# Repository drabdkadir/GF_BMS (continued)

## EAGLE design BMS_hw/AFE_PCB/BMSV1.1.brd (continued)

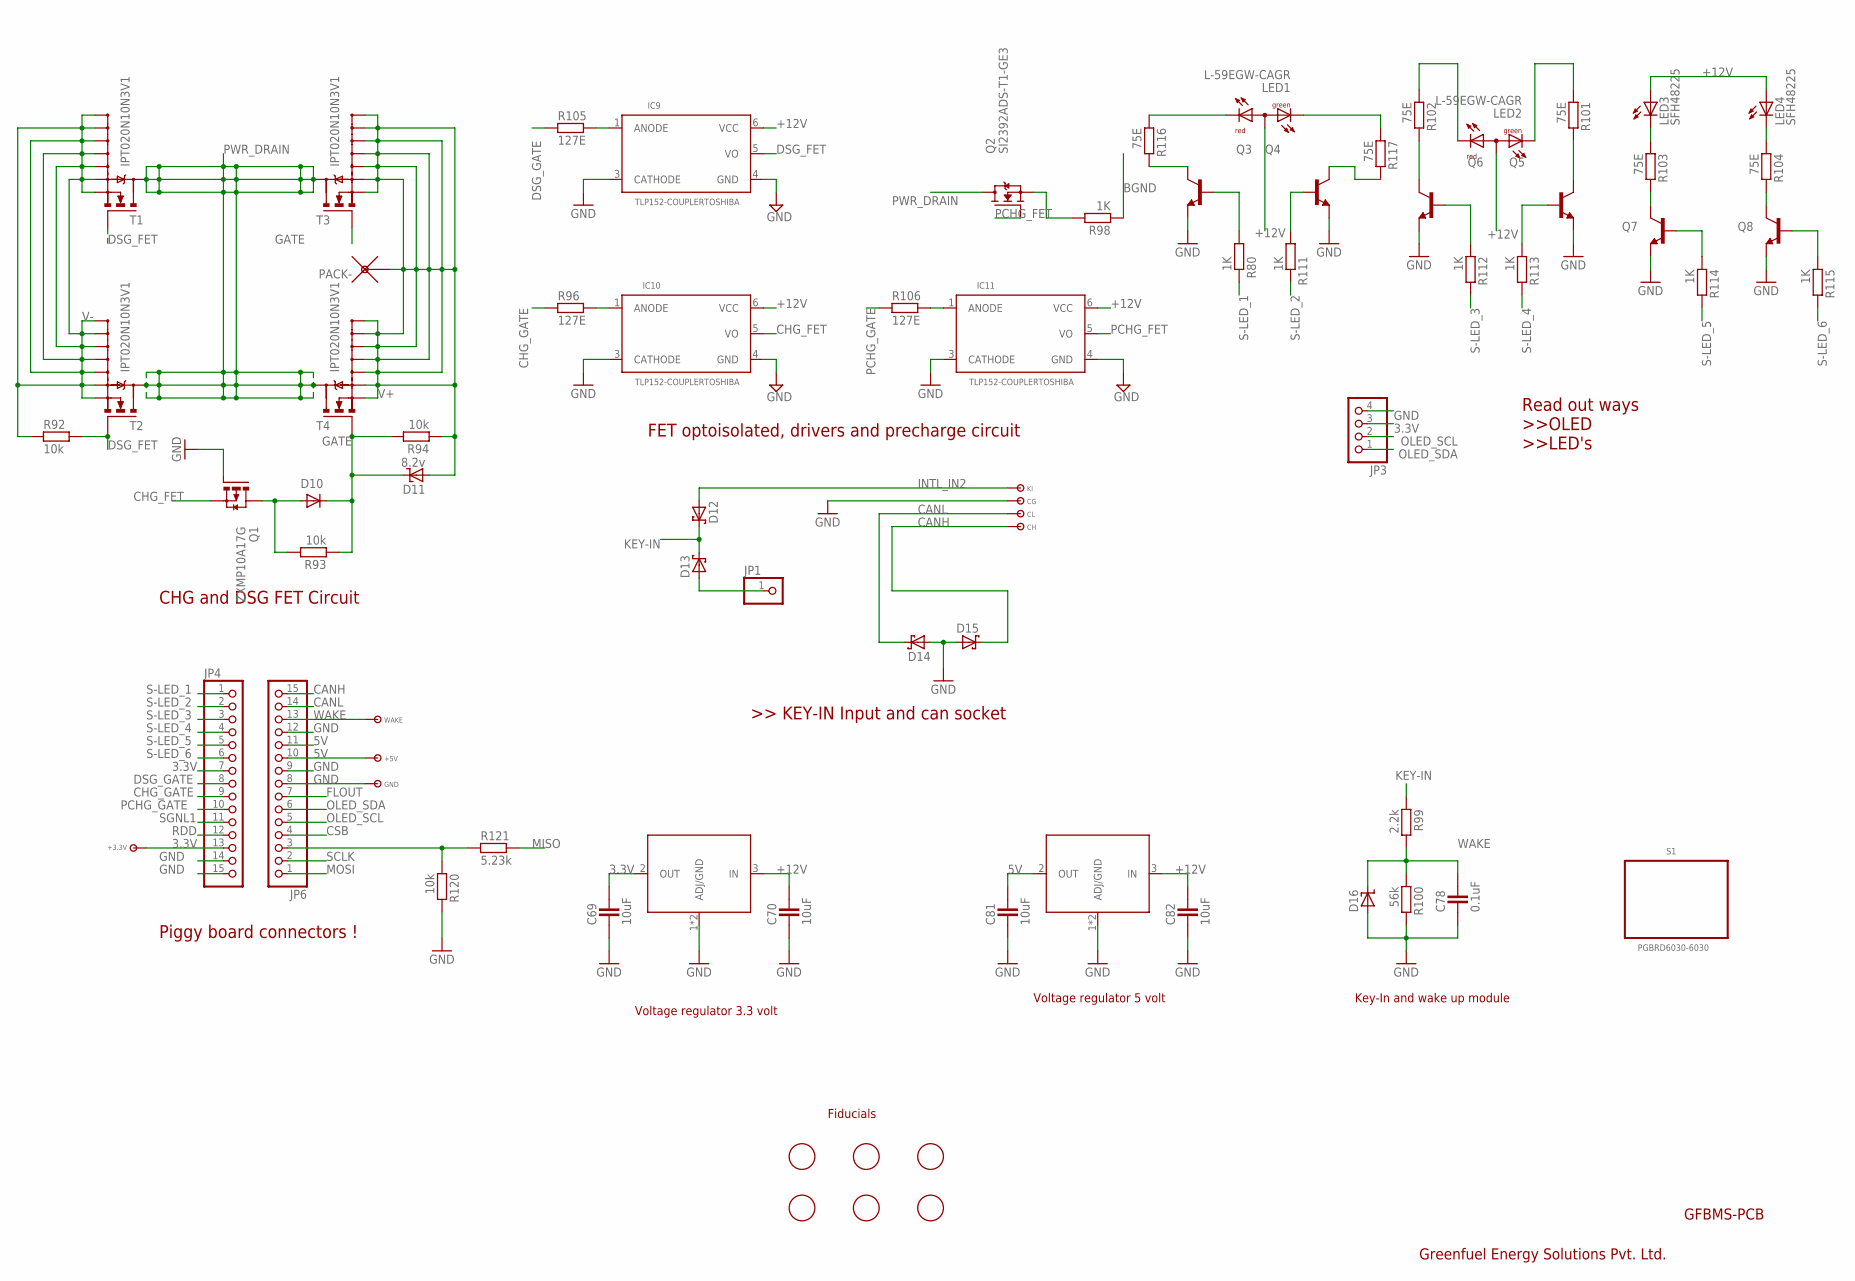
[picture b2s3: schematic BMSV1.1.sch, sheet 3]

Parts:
+3.3V, +5V: TP-SMD60
C69, C70, C81, C82: 10uF; CAPC2012X145AN
C78: 0.1uF; CAPC1608X92N
CG: TPTH7035; TP7035
CH: TPTH7035; TP7035
CL: TPTH7035; TP7035
D10: DIODE_SOD-123; SOD3718X135N
D11: 8.2v; SOD3718X135N
D12, D13, D14, D15: SCHOTTKY_SOD-123; SOD3718X135N
D16: ZENER_SOD-323; SOD2514X100N
FD1, FD2, FD3, FD4, FD5, FD6: FIDUCIAL; FIDUCIAL_1MM
GND: TP-SMD60
IC9, IC10, IC11: TLP152-COUPLERTOSHIBA; SO6-5PIN
JP1: PINHD-1X1CB; 1X01-CLEANBIG
JP3: PINOLED-4; OLED-CON
JP4, JP6: PINHD-1X15; 1X15
KI: TPTH7035; TP7035
LED1, LED2: L-59EGW-CAGR; L-59EGW-CA
LED3, LED4: SFH48225; SFH482
PACK-: WPAD
Q1: ZXMP10A17G; SOT23-3
Q2: SI2392ADS-T1-GE3; SOT23-3
Q3, Q4, Q5, Q6, Q7, Q8: NPN_SOT-23; SOT95P280X135-3N
R80, R111, R112, R113, R114, R115: 1K; RESC1005X40AN
R92, R93, R94: 10k; RESC1005X40AN
R96, R105, R106: 127E; RESC1608X55N
R98: 1K; RESC5025X70N
R99: 2.2k; RESC1608X55N
R100: 56k; RESC1608X55N
R101, R102, R103, R104, R116, R117: 75E; RESC1005X40AN
R120: 10k; RESC1608X55N
R121: 5.23k; RESC1608X55N
S1: PGBRD6030-6030; PIG6030
T1, T2, T3, T4: IPT020N10N3V1; PG-HSOF-9
U1: NCV1117ST33T3G; SOT-223
U2: NCV1117ST50T3G; SOT-223
WAKE: TP-SMD60

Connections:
3.3V: +3.3V.P$1, C69.2, JP3.3, JP4.7, JP4.13, U1.2 (OUT); also elsewhere on the board
5V: +5V.P$1, C81.2, JP6.10, JP6.11, U2.2 (OUT)
+12V: C70.2, C82.2, IC9.6 (VCC), IC10.6 (VCC), IC11.6 (VCC), LED1.2 (A), LED2.2 (A), LED3.A, LED4.A, U1.3 (IN), U2.3 (IN); also elsewhere on the board
BGND: R98.1; also elsewhere on the board
CANH: CH.P$1, D15.K, JP6.15
CANL: CL.P$1, D14.K, JP6.14
CHG_FET: IC10.5 (VO), Q1.2 (S)
CHG_GATE: JP4.9, R96.1
CSB: JP6.4; also elsewhere on the board
DSG_FET: IC9.5 (VO), R92.2, T1.1 (G), T2.1 (G)
DSG_GATE: JP4.8, R105.1
FLOUT: JP6.7; also elsewhere on the board
GATE: D10.K, D11.K, R93.1, R94.2, T3.1 (G), T4.1 (G)
GND: C69.1, C70.1, C78.1, C81.1, C82.1, CG.P$1, D14.A, D15.A, D16.A, GND.P$1, IC9.3 (CATHODE), IC9.4 (GND), IC10.3 (CATHODE), IC10.4 (GND), IC11.3 (CATHODE), IC11.4 (GND), JP3.4, JP4.14, JP4.15, JP6.8, JP6.9, JP6.12, Q1.1 (G), Q3.2 (E), Q4.2 (E), Q5.2 (E), Q6.2 (E), Q7.2 (E), Q8.2 (E), R100.2, R120.2, U1.1 (ADJ/GND), U1.4 (ADJ/GND), U2.1 (ADJ/GND), U2.4 (ADJ/GND); also elsewhere on the board
INTL_IN2: D12.A, KI.P$1
KEY-IN: D12.K, D13.K, R99.1
MISO: R121.2; also elsewhere on the board
MOSI: JP6.1; also elsewhere on the board
unnamed: D10.A, Q1.3 (D), R93.2
unnamed: IC9.1 (ANODE), R105.2
unnamed: Q7.3 (C), R103.2
unnamed: Q2.2 (S), R98.2
unnamed: Q8.3 (C), R104.2
unnamed: Q3.1 (B), R80.1
unnamed: IC10.1 (ANODE), R96.2
unnamed: IC11.1 (ANODE), R106.2
unnamed: Q4.1 (B), R111.1
unnamed: Q6.1 (B), R112.1
unnamed: Q5.1 (B), R113.1
unnamed: Q7.1 (B), R114.1
unnamed: Q8.1 (B), R115.1
unnamed: LED1.3 (CR), R116.1
unnamed: Q3.3 (C), R116.2
unnamed: LED1.1 (CG), R117.1
unnamed: Q6.3 (C), R102.2
unnamed: Q5.3 (C), R101.2
unnamed: Q4.3 (C), R117.2
unnamed: LED2.3 (CR), R102.1
unnamed: LED2.1 (CG), R101.1
unnamed: JP6.3, R120.1, R121.1
unnamed: LED4.K (C), R104.1
unnamed: LED3.K (C), R103.1
unnamed: D13.A, JP1.1
OLED_SCL: JP3.2, JP6.5
OLED_SDA: JP3.1, JP6.6
PCHG_FET: IC11.5 (VO), Q2.1 (G)
PCHG_GATE: JP4.10, R106.1
PWR_DRAIN: Q2.3 (D), T1.9 (D), T2.9 (D), T3.9 (D), T4.9 (D)
RDD: JP4.12; also elsewhere on the board
S-LED_1: JP4.1, R80.2
S-LED_2: JP4.2, R111.2
S-LED_3: JP4.3, R112.2
S-LED_4: JP4.4, R113.2
S-LED_5: JP4.5, R114.2
S-LED_6: JP4.6, R115.2
SCLK: JP6.2; also elsewhere on the board
SGNL1: JP4.11; also elsewhere on the board
V+: D11.A, PACK-.1, R94.1, T3.2 (S), T3.3 (S1), T3.4 (S2), T3.5 (S3), T3.6 (S4), T3.7 (S5), T3.8 (S6), T4.2 (S), T4.3 (S1), T4.4 (S2), T4.5 (S3), T4.6 (S4), T4.7 (S5), T4.8 (S6); also elsewhere on the board
V-: R92.1, T1.2 (S), T1.3 (S1), T1.4 (S2), T1.5 (S3), T1.6 (S4), T1.7 (S5), T1.8 (S6), T2.2 (S), T2.3 (S1), T2.4 (S2), T2.5 (S3), T2.6 (S4), T2.7 (S5), T2.8 (S6); also elsewhere on the board
WAKE: C78.2, D16.K, JP6.13, R99.2, R100.1, WAKE.P$1

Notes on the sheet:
CHG and DSG FET Circuit
Read out ways >>OLED >>LED's
FET optoisolated, drivers and precharge circuit
Piggy board connectors !
GFBMS-PCB
Greenfuel Energy Solutions Pvt. Ltd.
Key-In and wake up module
Voltage regulator 3.3 volt
Voltage regulator 5 volt
Fiducials

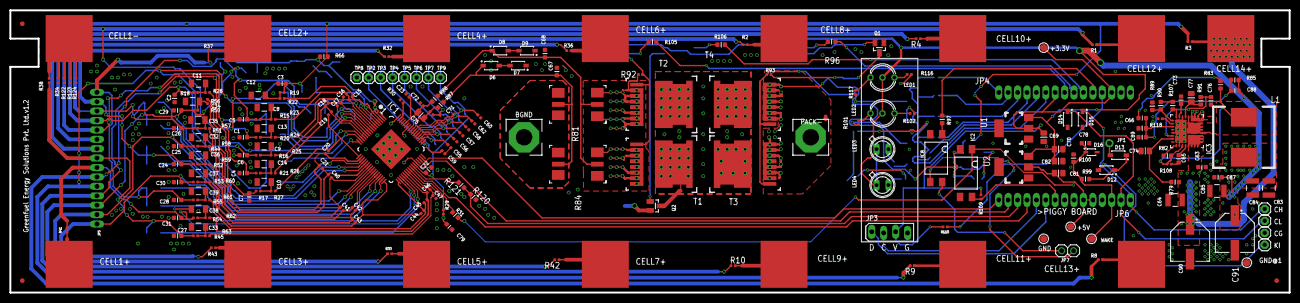
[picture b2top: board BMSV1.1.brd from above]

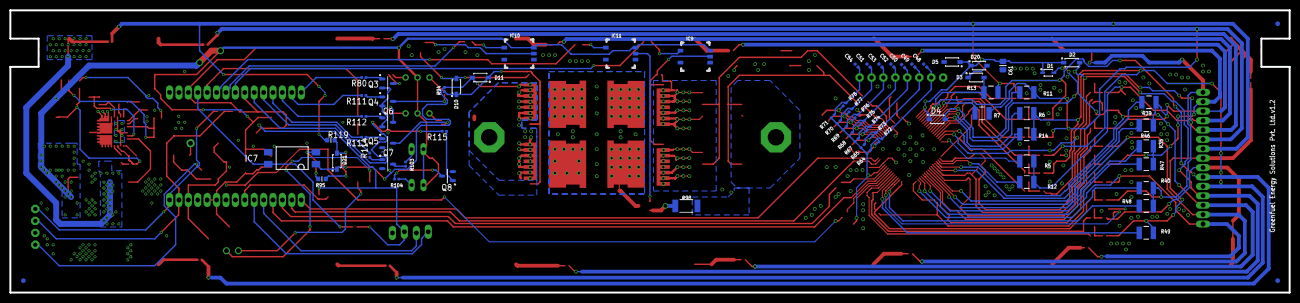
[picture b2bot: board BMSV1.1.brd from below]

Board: 2 copper layers, 272.0 x 60.0 mm, 305 parts (70 on the bottom side), 180 nets.

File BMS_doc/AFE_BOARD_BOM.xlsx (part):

GF_AFE board Revised: Sunday, OCT 14, 2018
SCH-XXXXX PDF: SPF-XXXXX Revision: 01
Item | Quantity | ASSY_OPT | Reference | Value | Description | ASSY_NOTE | Mfg Name | Mfg Part Number | PCB Footprint
1 | 17 |  | C1, C2, C3, C4, C5, C6, C7, C24, C25, C26, C27, C28, C29, C30, C31,C67, C68 | 0.047uF | CAP CER 0.047uF 100V 10% X7R AEC-Q200 0603 |  | KEMET | C0603C473K1RACAUTO | CC0603_OV | 17 | 0
2 | 18 |  | C15, C16, C17, C18, C19, C20, C21,C23, C40, C41, C42, C43, C44, C45, C46, C47,C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 | 0.047uF | CAP CER 0.047uF 50V 10% X7R AEC-Q200 0402 |  | TDK | CGA2B3X7R1H473K050BB | CC0402_25 | 18 | 0
3 | 2 |  | C22, C76 | 2.2uF | CAP CER 2.2uF 6.3V 10% X7R AEC-Q200 0603 |  | MURATA | GCM188R70J225KE22D | CC0603_OV | 2 | 0
4 | 7 |  | C48, C49, C50, C51, C52, C53, C54 | 2200pF | CAP CER 2200pF 50V 10% X7R AEC-Q200 0402 |  | MURATA | GCM155R71H222KA37D | CC0402_25 | 7 | 0
5 | 7 |  | C55,C56,C57,C58,C59,C60,C62 | 1000pF | CAP CER 1000PF 50V 10% X7R 0402 |  | AVX | 04025C102KAT2A | CC0402_25 | 7 | 0
6 | 1 |  | C61 | 0.22uF | CAP CER 0.22UF 100V 20% X7S 0805 |  | TDK | C2012X7S2A224M/SOFT | CC0805_OV | 1 | 0
7 | 3 |  | C63,C65,C66 | 0.1uF 100V | Capacitor ceramic, 10%, X7R,SMD, 0603 |  | Murata Electronics North America, Inc. | GRM188R72A104KA35D | SMD0603 | 3 | 0
8 | 1 |  | C64 | 2.2uF 100V | Capacitor cermaic, 100V, 10%, X7R, SMD, 1210 |  | KEMET | C1210C225K1RACTU | SMD1210 | 1 | 0
9 | 2 |  | C69,C81 | 10uF 25V | 10µF ±10% 25V Ceramic Capacitor X5R 0805 (2012 Metric) |  | Yageo | CC0805KKX5R8BB106 | SMD0805 | 2 | 0
10 | 2 |  | C70,C82 | 10uF 16V | 10µF ±10% 16V Ceramic Capacitor X5R 0805 (2012 Metric) |  | Yageo | CC0805KRX5R7BB106 | SMD0805 | 2 | 0
11 | 1 |  | C73 | 2.2uF 16V | Capacitor ceramic, 16V, 10%, X5R, SMD, 0603 |  | TDK Corporation | C1608X5R1C225K | SMD0603 | 1 | 0
12 | 1 |  | C74 | 1uF 100V | Capacitor ceramic, 1 µF, 100V, 10%, X7S,SMD, 0805 |  | TDK Corporation | C2012X7S2A105K125AB |  | 1 | 0
13 | 1 |  | C75 | 6.8uF | CAP CER 6.8uF 16V 10% X7S AEC-Q200 0805 |  |  | CGA4J1X7S1C685K125AC | change package to 0805 | 1 | 0
14 | 1 |  | C77 | 4.7uF 25V | Capacitor ceramic, 25V, 20%, Y5V |  | TDK Corporation | C2012Y5V1E475Z | SMD0805 | 1 | 0
15 | 2 |  | C78,C79 | 0.1uF | CAP CER 0.1UF 50V 5% X7R 0603 |  | AVX | 06035C104JAT2A | CC0603_OV | 2 | 0
16 | 15 |  | C8, C9, C10, C11, C12, C13, C14, C32, C33, C34, C35, C36, C37, C38, C39 | 0.47uF | CAP CER 0.47uF 100V 5% X7R 1206 |  | KEMET | C1206C474J1RACTU | CC1206_OV | 15 | 0
17 | 3 |  | C83, C84, C85 | 47uF 16V | Capacitor ceramic, 47 µF, 16V, 20%, X5R, SMD, 1210 |  |  | CC1210MKX5R7BB476 | SMD1210 | 3 | 0
18 | 1 |  | C87 | 0.1uF 16V | Capacitor ceramic, 10%, X7R,SMD, 0603 |  | AVX Corporation | 0603YC104KAT2A | SMD0603 | 1 | 0
19 | 1 |  | C88 | 4700pF 50V | Capacitor ceramic, 50V, 10%, X7R, SMD , 0603 |  | KEMET | C0603C472K5RACTU | SMD0603 | 1 | 0
20 | 1 | DNP | C89 | 10pF 50V | Capacitor ceramic, 50V, SMD , 0603 |  | TDK Corporation | C1608C0G1H100D | SMD0603 | 1 | 0
21 | 1 |  | C90 | 39uF 100V | Capacitor aluminum, 39 µF, 100V, 20%, RAD |  |  |  | POLAR CAP SMD | 1 | 0
 | 1 |  | C91 | 330uF 25V |  |  |  |  |  | 1 | 0
22 | 1 |  | D1 | MM3Z47VB | DIODE ZNR -- 47V 0.2W SOD323 |  | FAIRCHILD | MM3Z47VB | sod323_1A | 1 | 0
23 | 1 |  | D10 | CGRM4007-G | DIODE RECT GEN 1A 1000V SMA |  | COMCHIP TECHNOLOGY CO., LTD | CGRM4007-G | sod123_b | 1 | 0
24 | 4 |  | D12,D13,D14,D15 | MMSZ5267BT1G | DIODE ZNR 1.7MA 0.5W 75V AEC-Q101 SOD-123 |  | ON Semiconductor | MMSZ5267BT1G | SOD-123 | 4 | 0
25 | 1 |  | D16 | PDZ4.3B | DIODE ZNR 4.3V 5MA 400MW SOD323 |  | NXP Semiconductors | PDZ4.3B,115 | sod-323-A | 1 | 0
26 | 1 |  | D2 | MMSZ5257BT1G | DIODE ZNR 500mW 33V AEC-Q101 SOD123 |  | ON Semiconductor | MMSZ5257BT1G | SOD-123 | 1 | 0
27 | 4 |  | D3, D20, D21, D11 | 8.2V | DIODE ZNR 20MA 8.2V 0.5W AEC-Q101 SOD123 |  | On semiconductor | MMSZ5237BT1G | sod123 | 4 | 0
28 | 1 |  | D4 | MMSZ5257BT1G | DIODE ZNR 500mW 33V AEC-Q101 SOD123 |  | ON Semiconductor | MMSZ5257BT1G | SOD-123 | 1 | 0
29 | 1 |  | D5 | MMSZ5267BT1G | DIODE ZNR 1.7MA 0.5W 75V AEC-Q101 SOD-123 |  | ON Semiconductor | MMSZ5267BT1G | SOD-123 | 1 | 0
30 | 4 |  | D6, D7, D8, D9 | 2V | Zener Diode 2V 500mW ±5% Surface Mount SOD-123 |  |  | MMSZ4679T1G | SOD-123 | 4 | 0
31 | 1 |  | IC1 | MC33771ATP1AE | IC AUTOMOTIVE BMSIC 9.6-61.6V LQFP64 |  | FREESCALE SEMICONDUCTOR | PC33771ATP1AE | LQFP64_EP205MIL | 1 | 0
32 | 3 |  | IC2, IC7, IC8 | OPTOCOUPLER | Optoisolator Transistor Output 5300Vrms 1 Channel 4-SMD |  |  | SFH6156-3T | 4-SMD | 3 | 0
33 | 1 |  | IC3 | MIC28515T-E | MCHP Analog Switcher Buck |  | Microchip Technology Inc. | MIC28515T-E/PHA | VQFN-32 | 1 | 0
34 | 3 |  | IC9, IC10, IC11 |  | 2.5A Gate Driver Optical Coupling 3750Vrms 1 Channel 6-SO, 5 Lead |  | TOSIBHA | TLP152(TPL,E | SO6-5PIN | 3 | 0
35 | 2 |  | JP4,JP6 |  | 15 POSITION 1 ROW 2MM PITCH STRAIGHT B2B HEADERS |  |  |  | PINHD-1X15 | 2 | 0
36 | 1 |  | JP5 |  | 15 POSITION 1 ROW 2MM PITCH RIGHT ANGLE W2B HEADERS |  |  |  | PINHD-1X15 | 1 | 0
37 | 1 |  | JP7 |  | 2 POSITION 1 ROW 2.54MM PITCH STRAIGHT W2B HEADERS |  |  |  | PINHD-1X2 | 1 | 0
38 | 1 |  | L1 | BUCK COIL | Fixed Inductors MSS1278T AEC-Q200 22 uH 20% 4A Ferrite |  |  | MSS1278T-223MLD | MSS1278-D | 1 | 0
39 | 2 |  | LED1, LED2 | LED | Common Anode GREEN,Red 5MM |  |  |  | L-59EGW-CA | 2 | 0
40 | 1 |  | LED4 |  | RED LED 3MM |  |  |  | SFH482 | 1 | 0
40 | 1 |  | LED3 |  | Green LED 3MM |  |  |  | SFH482 | 1 | 0
41 | 1 |  | Q1 | 80V 2.2A | P-Channel 80V 2.2A (Tc) 3W (Tc) Surface Mount SOT-23-3 (TO-236) |  |  | SQ2337ES-T1_GE3 | sot23-3 | 1 | 0
42 | 1 |  | Q2 | 100V 3.1A | N-Channel 100V 3.1A (Tc) 1.25W (Ta), 2.5W (Tc) Surface Mount SOT-23-3 (TO-236) |  |  | SI2392ADS-T1-GE3 | SOT23-3 | 1 | 0
43 | 6 |  | Q3, Q4, Q5, Q6, Q7, Q8 | NPN 40V .2A | Bipolar (BJT) Transistor NPN 40V 200mA 300MHz 350mW Surface Mount SOT-23-3 |  | ON Semiconductor | MMBT3904 | SOT-23 | 6 | 0
44 | 18 |  | R1,R2,R3,R4,R8,R9,R10,R32,R33,R34,R36,R37,R38,R41,R42,R43, R108,R118 | 0E | RES TF ZERO OHM 1/16W AEC-Q200 RC0402 |  | VISHAY INTERTECHNOLOGY | CRCW04020000ZS | RC0402_25 | 18 | 0
45 | 1 |  | R100 | 56K |  |  |  | CRCW060356K0JNEA | SMD0402 | 1 | 0
46 | 6 |  | R101,R102,R116,R117,R103,R104 | 75E |  |  |  | RCS040275R0FKED | SMD0402 | 6 | 0
48 | 15 |  | R15, R16, R17, R18, R19, R20, R21, R44, R45, R50, R51, R52, R53, R54, R55 | 3.0K | RES MF 3.0K 1/16W 1% 0402 |  | KOA SPEER | RK73H1ETTP3001F | RC0402_25 | 15 | 0
49 | 15 |  | R22, R23, R24, R25, R26, R27, R28, R56, R57, R58, R59, R60, R61, R62, R63 | 2.00k | RES MF 2K 1/16W 1% AEC-Q200 0402 |  | KOA SPEER | RK73H1ETTP2001F | RC0402_25 | 15 | 0
50 | 14 |  | R29, R30, R64, R65, R67, R68, R69, R70, R71, R92, R93,R94,R109,R110 | 10.0K | RES MF 10.0K 1/16W 1% AEC-Q200 0402 |  | KOA SPEER | RK73H1ETTP1002F | RC0402_25 | 14 | 0
52 | 14 |  | R5, R6,R7, R11, R12, R13, R14, R35, R39, R40, R46, R47, R48, R49 | 39E | RES MF 39 OHM 0.75W 1% AEC-Q200 1210 |  | VISHAY INTERTECHNOLOGY | CRCW121039R0FKEAHP | RC1210 | 14 | 0
53 | 1 |  | R66 | 10E | RES MF 10.0 OHM 1/10W 1% 0603 |  | KOA SPEER | RK73H1JTTD10R0F | RC0603_OV | 1 | 0
54 | 7 |  | R72, R73, R74, R75, R76, R77, R78 | 1.0K | RES MF 1.0K 1/16W 1% 0402 |  | YAGEO AMERICA | RC0402FR-071KL | RC0402_25 | 7 | 0
55 | 1 |  | R79 | 2E | Resistor, TKF, 1%, 1/4W, SMD, 0603 |  | Vishay/Dale | CRCW06032R00FKEAHP | SMD0603 | 1 | 0
56 | 2 |  | R81, R84 | 200uOhm |  |  |  | LRMAP3920SUNT | LRMAP3920 | 2 | 0
57 | 1 |  | R82 | 1.6K | Resistor, 1%,1/10W, SMD, 0603 |  | Vishay/Dale | CRCW06031K60FKEA | SMD0603 | 1 | 0
58 | 1 |  | R83 | 16.2K | Resistor, TKF,1%,1/10W,SMD,0603 |  | Panasonic -ECG | ERJ-3EKF1622V | SMD0603 | 1 | 0
59 | 1 |  | R85 | 10K | Resistor, TF,1%,1/8W,SMD,0603 |  | Vishay Beyschlag | MCT06030C1002FP500 | SMD0603 | 1 | 0
60 | 1 |  | R86 | 523E |  |  |  | ERJ3EKF5230V | SMD0603 | 1 | 0
61 | 9 |  | R87, R88, R96, R105, R106,R31, R95, R97, R119 | 127E | RES MF 127 OHM 1/10W 1% 0603 |  | KOA SPEER | RK73H1JTTD1270F | RC0603_OV | 9 | 0
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
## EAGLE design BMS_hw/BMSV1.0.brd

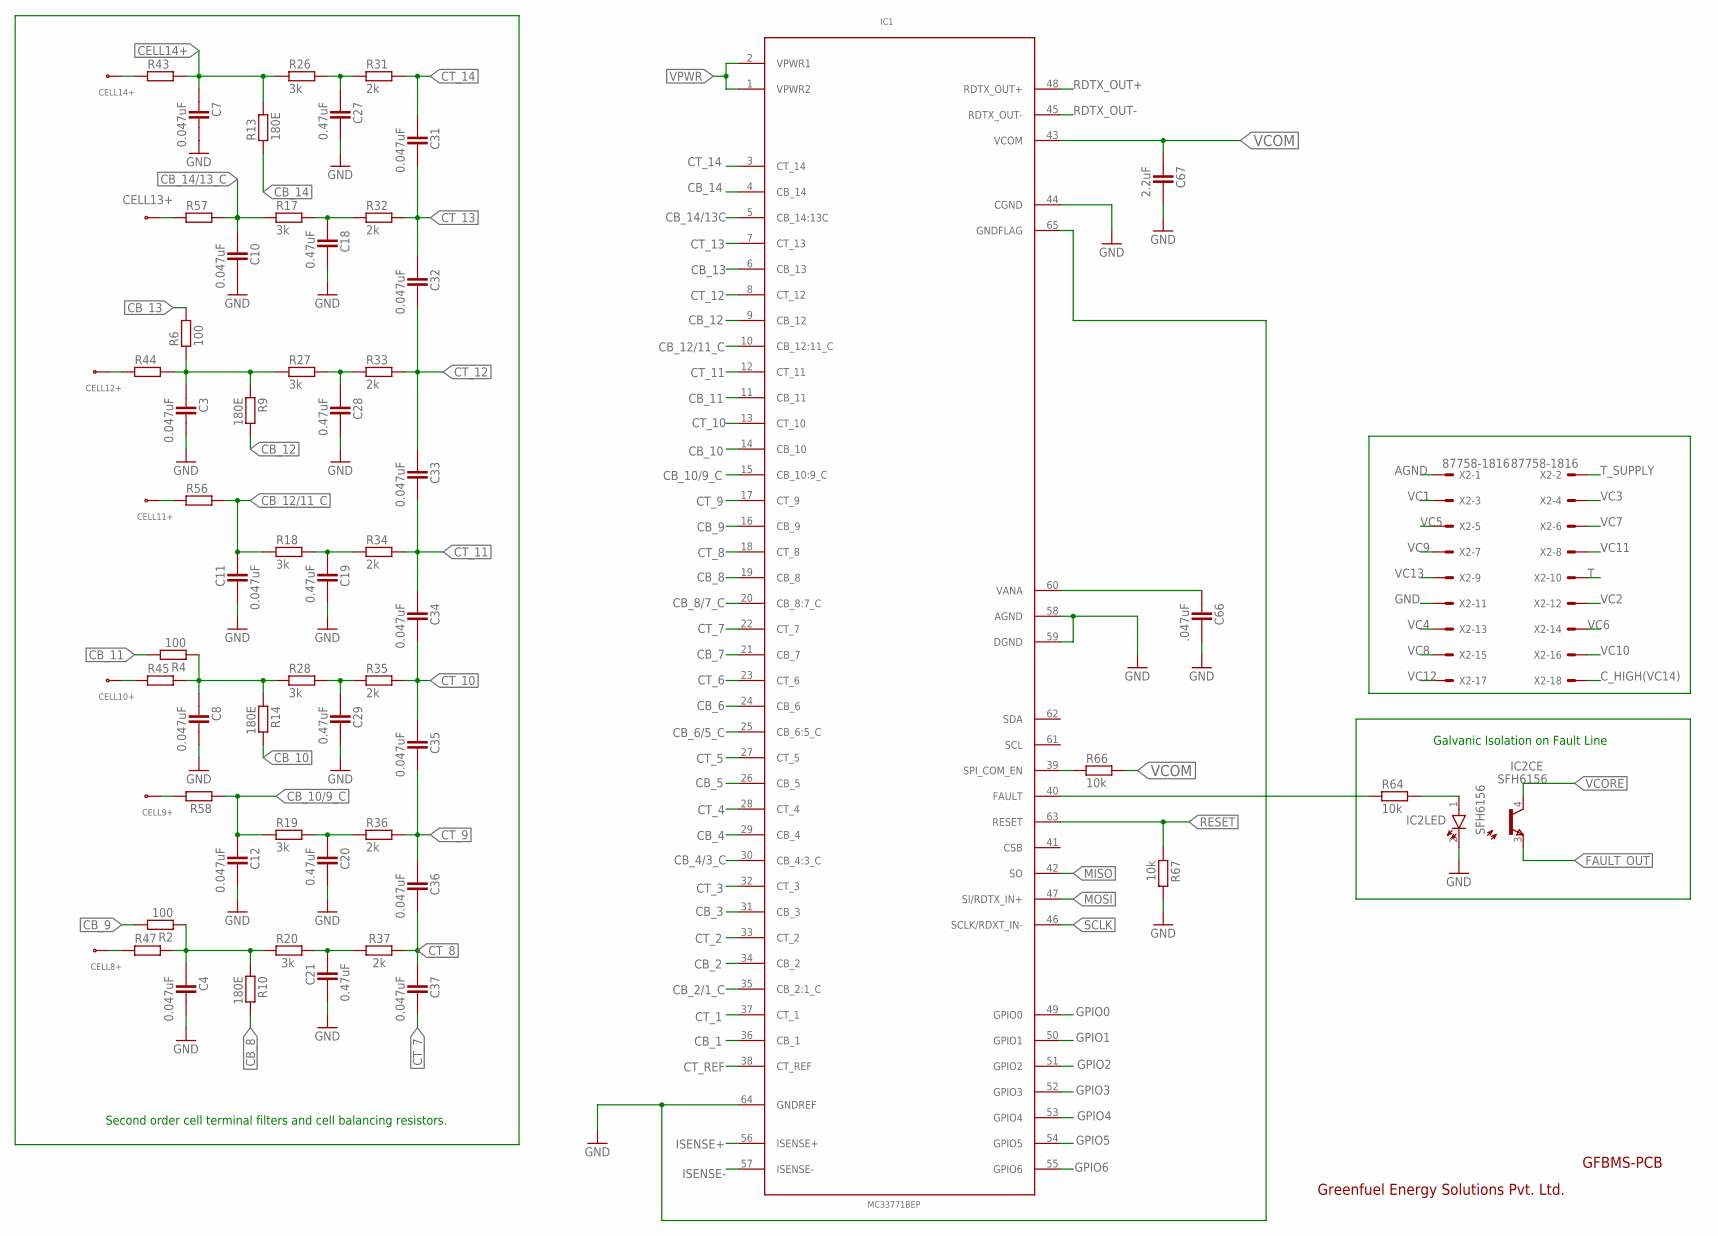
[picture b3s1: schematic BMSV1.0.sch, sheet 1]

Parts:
C3, C4, C7, C8, C10, C11, C12, C31, C32, C33, C34, C35, C36, C37: 0.047uF; CAPC1005X60N
C18, C19, C20, C21, C27, C28, C29: 0.47uF; CAPC1005X60N
C66: .047uF; CAPC1005X60N
C67: 2.2uF; CAPC1005X60N
CELL8+, CELL9+, CELL10+, CELL11+, CELL12+, CELL13+, CELL14+: GF_BMS_CELL_PADP_PAD; CELL_PAD
IC1: MC33771BEP; 64PIN-LQFP
IC2: SFH6156; SFH
R2, R4, R6: 100; RESC1005X40AN
R9, R10, R13, R14: 180E; RESC1005X40AN
R17, R18, R19, R20, R26, R27, R28: 3k; RESC1005X40AN
R31, R32, R33, R34, R35, R36, R37: 2k; RESC1005X40AN
R43, R44, R45, R47, R56, R57, R58: RESISTOR_0402; RESC1005X40AN
R64, R66, R67: 10k; RESC1005X40AN
X2: 87758-1816

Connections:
AGND: X2.1
CB_1: IC1.36 (CB_1); also elsewhere on the board
CB_2: IC1.34 (CB_2); also elsewhere on the board
CB_2/1_C: IC1.35 (CB_2:1_C); also elsewhere on the board
CB_3: IC1.31 (CB_3); also elsewhere on the board
CB_4: IC1.29 (CB_4); also elsewhere on the board
CB_4/3_C: IC1.30 (CB_4:3_C); also elsewhere on the board
CB_5: IC1.26 (CB_5); also elsewhere on the board
CB_6: IC1.24 (CB_6); also elsewhere on the board
CB_6/5_C: IC1.25 (CB_6:5_C); also elsewhere on the board
CB_7: IC1.21 (CB_7); also elsewhere on the board
CB_8: IC1.19 (CB_8), R10.2
CB_8/7_C: IC1.20 (CB_8:7_C); also elsewhere on the board
CB_9: IC1.16 (CB_9), R2.2
CB_10: IC1.14 (CB_10), R14.2
CB_10/9_C: C12.1, IC1.15 (CB_10:9_C), R19.1, R58.1; also elsewhere on the board
CB_11: IC1.11 (CB_11), R4.2
CB_12: IC1.9 (CB_12), R9.2; also elsewhere on the board
CB_12/11_C: C11.1, IC1.10 (CB_12:11_C), R18.1, R56.2
CB_13: IC1.6 (CB_13), R6.2
CB_13/12_C: C3.1, R6.1, R9.1, R27.1, R44.2
CB_13/12_C1: C8.1, R4.1, R14.1, R28.1, R45.2
CB_13/12_C2: C4.1, R2.1, R10.1, R20.1, R47.2
CB_14: IC1.4 (CB_14), R13.1; also elsewhere on the board
CB_14/13C: IC1.5 (CB_14:13C)
CB_14/13_C: C10.1, R17.1, R57.2
CELL14+: C7.1, R13.2, R26.1, R43.2; also elsewhere on the board
CT_1: IC1.37 (CT_1); also elsewhere on the board
CT_2: IC1.33 (CT_2); also elsewhere on the board
CT_3: IC1.32 (CT_3); also elsewhere on the board
CT_4: IC1.28 (CT_4); also elsewhere on the board
CT_5: IC1.27 (CT_5); also elsewhere on the board
CT_6: IC1.23 (CT_6); also elsewhere on the board
CT_7: C37.2, IC1.22 (CT_7); also elsewhere on the board
CT_8: C36.2, C37.1, IC1.18 (CT_8), R37.2
CT_9: C35.2, C36.1, IC1.17 (CT_9), R36.2
CT_10: C34.2, C35.1, IC1.13 (CT_10), R35.2
CT_11: C33.2, C34.1, IC1.12 (CT_11), R34.2
CT_12: C32.2, C33.1, IC1.8 (CT_12), R33.2
CT_13: C31.2, C32.1, IC1.7 (CT_13), R32.2
CT_14: C31.1, IC1.3 (CT_14), R31.2
CT_REF: IC1.38 (CT_REF); also elsewhere on the board
C_HIGH(VC14): X2.18
FAULT_OUT: IC2.3 (E)
GND: C3.2, C4.2, C7.2, C8.2, C10.2, C11.2, C12.2, C18.2, C19.2, C20.2, C21.2, C27.2, C28.2, C29.2, C66.2, C67.2, IC1.44 (CGND), IC1.58 (AGND), IC1.59 (DGND), IC1.64 (GNDREF), IC1.65 (GNDFLAG), IC2.2 (K), R67.2, X2.11; also elsewhere on the board
GPIO0: IC1.49 (GPIO0); also elsewhere on the board
GPIO1: IC1.50 (GPIO1); also elsewhere on the board
GPIO2: IC1.51 (GPIO2); also elsewhere on the board
GPIO3: IC1.52 (GPIO3); also elsewhere on the board
GPIO4: IC1.53 (GPIO4); also elsewhere on the board
GPIO5: IC1.54 (GPIO5); also elsewhere on the board
GPIO6: IC1.55 (GPIO6); also elsewhere on the board
ISENSE+: IC1.56 (ISENSE+); also elsewhere on the board
ISENSE-: IC1.57 (ISENSE-); also elsewhere on the board
MISO: IC1.42 (SO)
MOSI: IC1.47 (SI/RDTX_IN+)
unnamed: C27.1, R26.2, R31.1
unnamed: C21.1, R20.2, R37.1
unnamed: C29.1, R28.2, R35.1
unnamed: C28.1, R27.2, R33.1
unnamed: C18.1, R17.2, R32.1
unnamed: C20.1, R19.2, R36.1
unnamed: C19.1, R18.2, R34.1
unnamed: C66.1, IC1.60 (VANA)
unnamed 100: CELL14+.P$1, R43.1; also elsewhere on the board
unnamed: IC1.40 (FAULT), R64.1
unnamed: IC2.1 (A), R64.2
unnamed: IC1.39 (SPI_COM_EN), R66.1
unnamed: CELL12+.P$1, R44.1
unnamed: CELL10+.P$1, R45.1
unnamed: CELL8+.P$1, R47.1
unnamed: CELL11+.P$1, R56.1
unnamed: CELL13+.P$1, R57.1
unnamed: CELL9+.P$1, R58.2
RDTX_OUT+: IC1.48 (RDTX_OUT+); also elsewhere on the board
RDTX_OUT-: IC1.45 (RDTX_OUT-); also elsewhere on the board
RESET: IC1.63 (RESET), R67.1
SCLK: IC1.46 (SCLK/RDXT_IN-)
T: X2.10
T_SUPPLY: X2.2
VC1: X2.3
VC2: X2.12
VC3: X2.4
VC4: X2.13
VC5: X2.5
VC6: X2.14
VC7: X2.6
VC8: X2.15
VC9: X2.7
VC10: X2.16
VC11: X2.8
VC12: X2.17
VC13: X2.9
VCOM: C67.1, IC1.43 (VCOM), R66.2; also elsewhere on the board
VCORE: IC2.4 (C)
VPWR: IC1.1 (VPWR2), IC1.2 (VPWR1); also elsewhere on the board

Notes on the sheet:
Galvanic Isolation on Fault Line
Second order cell terminal filters and cell balancing resistors.
Greenfuel Energy Solutions Pvt. Ltd.
GFBMS-PCB

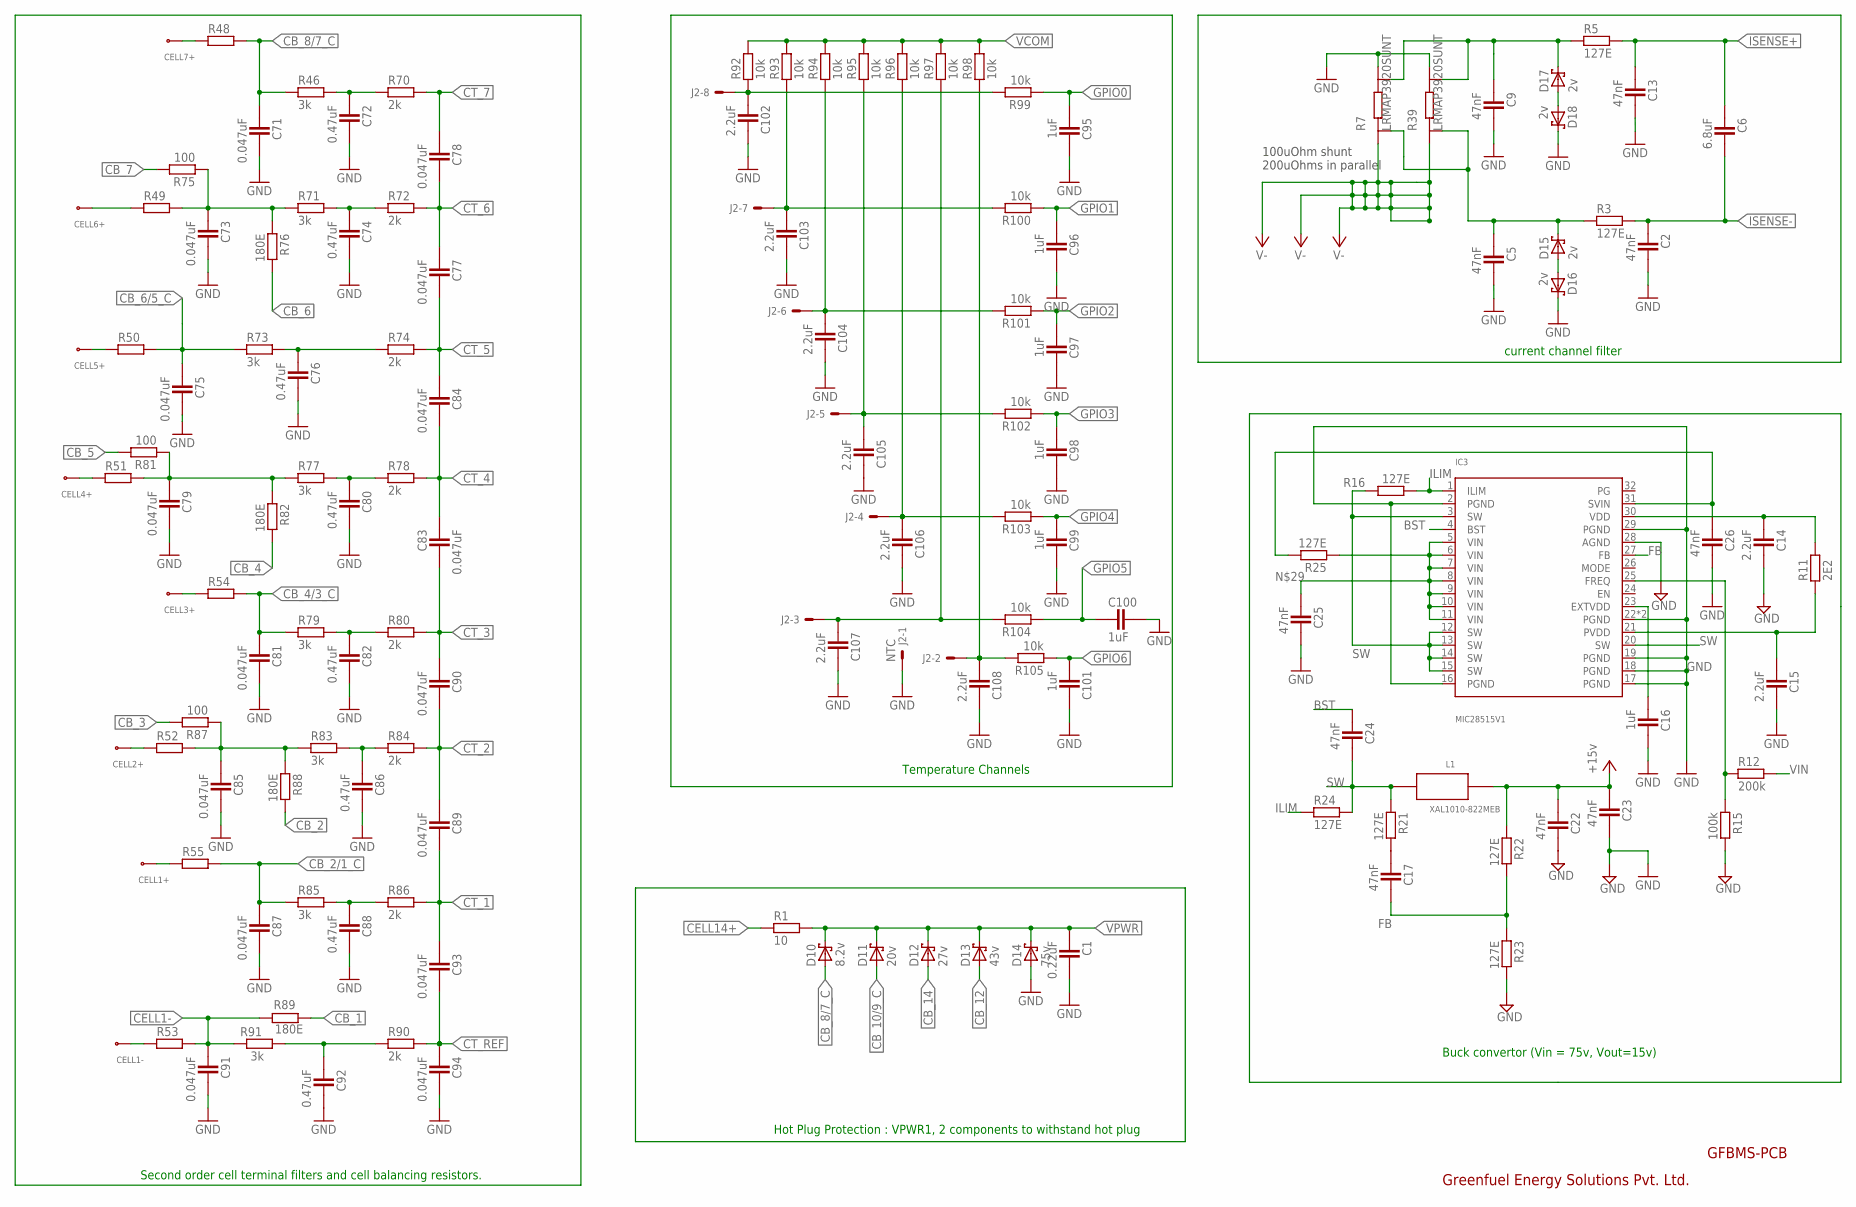
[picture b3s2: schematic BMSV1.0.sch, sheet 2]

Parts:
C1: 0.22uF; CAPC1005X60N
C2, C5, C9, C13, C17, C24, C26: 47nF; CAPC1005X60N
C6: 6.8uF; CAPC1005X60N
C14, C15, C102, C103, C104, C105, C106, C107, C108: 2.2uF; CAPC1005X60N
C16, C95, C96, C97, C98, C99, C100, C101: 1uF; CAPC1005X60N
C22: 47nF; CAPC1608X92N
C23, C25: 47nF; CAPC3225X168N
C71, C73, C75, C77, C78, C79, C81, C83, C84, C85, C87, C89, C90, C91, C93, C94: 0.047uF; CAPC1005X60N
C72, C74, C76, C80, C82, C86, C88, C92: 0.47uF; CAPC1005X60N
CELL1+, CELL1-, CELL2+, CELL3+, CELL4+, CELL5+, CELL6+, CELL7+: GF_BMS_CELL_PADP_PAD; CELL_PAD
D10: 8.2v; SOD3718X135N
D11: 20v; SOD3718X135N
D12: 27v; SOD3718X135N
D13: 43v; SOD3718X135N
D14: 75v; SOD3718X135N
D15, D16, D17, D18: 2v; SOD3718X135N
IC3: MIC28515V1; VQFN-32
J2: NTC; 6410-08
L1: XAL1010-822MEB; DUALPAD
R1: 10; RESC1005X40AN
R3, R5, R16, R21, R22, R23, R24, R25: 127E; RESC1005X40AN
R7, R39: LRMAP3920SUNT; SMD4
R11: 2E2; RESC1005X40AN
R12: 200k; RESC1005X40AN
R15: 100k; RESC1005X40AN
R46, R71, R73, R77, R79, R83, R85, R91: 3k; RESC1005X40AN
R48, R49, R50, R51, R52, R53, R54, R55: RESISTOR_0402; RESC1005X40AN
R70, R72, R74, R78, R80, R84, R86, R90: 2k; RESC1005X40AN
R75, R81, R87: 100; RESC1005X40AN
R76, R82, R88, R89: 180E; RESC1005X40AN
R92, R93, R94, R95, R96, R97, R98, R99, R100, R101, R102, R103, R104, R105: 10k; RESC1005X40AN

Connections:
BST: C24.1, IC3.4 (BST)
CB_1: R89.2; also elsewhere on the board
CB_2: R88.2; also elsewhere on the board
CB_2/1_C: C87.1, R55.2, R85.1; also elsewhere on the board
CB_3: R87.2; also elsewhere on the board
CB_4: R82.2; also elsewhere on the board
CB_4/3_C: C81.1, R54.2, R79.1; also elsewhere on the board
CB_5: R81.2; also elsewhere on the board
CB_6: R76.2; also elsewhere on the board
CB_6/5_C: C75.1, R50.2, R73.1; also elsewhere on the board
CB_7: R75.2; also elsewhere on the board
CB_8/7_C: C71.1, D10.A, R46.1, R48.2; also elsewhere on the board
CB_10/9_C: D11.A; also elsewhere on the board
CB_12: D13.A; also elsewhere on the board
CB_13/12_C6: C73.1, R49.2, R71.1, R75.1, R76.1
CB_13/12_C7: C79.1, R51.2, R77.1, R81.1, R82.1
CB_13/12_C8: C85.1, R52.2, R83.1, R87.1, R88.1
CB_14: D12.A; also elsewhere on the board
CELL1-: C91.1, R53.2, R89.1, R91.1
CELL14+: R1.1; also elsewhere on the board
CT_1: C89.2, C93.1, R86.2; also elsewhere on the board
CT_2: C89.1, C90.2, R84.2; also elsewhere on the board
CT_3: C83.2, C90.1, R80.2; also elsewhere on the board
CT_4: C83.1, C84.2, R78.2; also elsewhere on the board
CT_5: C77.2, C84.1, R74.2; also elsewhere on the board
CT_6: C77.1, C78.2, R72.2; also elsewhere on the board
CT_7: C78.1, R70.2; also elsewhere on the board
CT_REF: C93.2, C94.1, R90.2; also elsewhere on the board
FB: C17.2, IC3.27 (FB), R22.2, R23.1
GND: C1.2, C2.2, C5.2, C9.2, C13.2, C14.2, C15.2, C16.2, C22.2, C23.2, C25.2, C26.2, C71.2, C72.2, C73.2, C74.2, C75.2, C76.2, C79.2, C80.2, C81.2, C82.2, C85.2, C86.2, C87.2, C88.2, C91.2, C92.2, C94.2, C95.2, C96.2, C97.2, C98.2, C99.2, C100.2, C101.2, C102.2, C103.2, C104.2, C105.2, C106.2, C107.2, C108.2, D14.A, D16.K, D18.K, IC3.2 (PGND), IC3.16 (PGND), IC3.17 (PGND), IC3.18 (PGND), IC3.19 (PGND), IC3.22 (PGND), IC3.28 (AGND), IC3.29 (PGND), IC3.33 (PGND), J2.1, R7.4, R7.6 (4), R15.2, R23.2, R39.4, R39.6 (4); also elsewhere on the board
GPIO0: C95.1, R99.1; also elsewhere on the board
GPIO1: C96.1, R100.1; also elsewhere on the board
GPIO2: C97.1, R101.1; also elsewhere on the board
GPIO3: C98.1, R102.1; also elsewhere on the board
GPIO4: C99.1, R103.1; also elsewhere on the board
GPIO5: C100.1, R104.1; also elsewhere on the board
GPIO6: C101.1, R105.1; also elsewhere on the board
ILIM: IC3.1 (ILIM), R16.1, R24.1
ISENSE+: C6.1, C13.1, R5.2; also elsewhere on the board
ISENSE-: C2.1, C6.2, R3.2; also elsewhere on the board
unnamed: D15.A, D16.A
unnamed: C76.1, R73.2, R74.1
unnamed: D17.A, D18.A
unnamed: IC3.25 (FREQ), R12.1, R15.1
unnamed: C16.1, IC3.23 (EXTVDD)
unnamed: C26.1, IC3.31 (SVIN), R25.2
unnamed: C17.1, R21.2
unnamed 100: C25.1, IC3.5 (VIN), IC3.6 (VIN), IC3.7 (VIN), IC3.8 (VIN), IC3.9 (VIN), IC3.10 (VIN), IC3.11 (VIN), R25.1; also elsewhere on the board
unnamed: CELL6+.P$1, R49.1
unnamed: CELL5+.P$1, R50.1
unnamed: C72.1, R46.2, R70.1
unnamed: C74.1, R71.2, R72.1
unnamed: CELL7+.P$1, R48.1
unnamed: C80.1, R77.2, R78.1
unnamed: C82.1, R79.2, R80.1
unnamed: C86.1, R83.2, R84.1
unnamed: C88.1, R85.2, R86.1
unnamed: C92.1, R90.1, R91.2
unnamed: C102.1, J2.8, R92.1, R99.2
unnamed: C103.1, J2.7, R93.1, R100.2
unnamed: C104.1, J2.6, R94.1, R101.2
unnamed: C105.1, J2.5, R95.1, R102.2
unnamed: C106.1, J2.4, R96.1, R103.2
unnamed: C107.1, J2.3, R97.1, R104.2
unnamed: C108.1, J2.2, R98.1, R105.2
unnamed: CELL4+.P$1, R51.1
unnamed: CELL3+.P$1, R54.1
unnamed: CELL2+.P$1, R52.1
unnamed: CELL1+.P$1, R55.1
unnamed: CELL1-.P$1, R53.1
unnamed: C9.1, D17.K, R5.1, R7.5, R39.5
unnamed: C5.1, D15.K, R3.1, R7.2, R39.2
PVDD: C15.1, IC3.21 (PVDD), R11.1
SW: C24.2, IC3.3 (SW), IC3.12 (SW), IC3.13 (SW), IC3.14 (SW), IC3.15 (SW), IC3.20 (SW), L1.1, R16.2, R21.1, R24.2
V-: R7.1, R7.3 (1), R39.1, R39.3 (1)
VCC: C22.1, C23.1, L1.2, R22.1
VCOM: R92.2, R93.2, R94.2, R95.2, R96.2, R97.2, R98.2; also elsewhere on the board
VDD: C14.1, IC3.30 (VDD), R11.2; also elsewhere on the board
VIN: R12.2
VPWR: C1.1, D10.K, D11.K, D12.K, D13.K, D14.K, R1.2; also elsewhere on the board

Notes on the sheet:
Second order cell terminal filters and cell balancing resistors.
Temperature Channels
Hot Plug Protection : VPWR1, 2 components to withstand hot plug
current channel filter
100uOhm shunt 200uOhms in parallel
Greenfuel Energy Solutions Pvt. Ltd.
GFBMS-PCB
Buck convertor (Vin = 75v, Vout=15v)
